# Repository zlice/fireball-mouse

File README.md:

# Fireball mouse

Small PMW3360 fingertip mouse with a magnetic hall sensor joystick for scrolling and single 'fire' button for enter.

Designed for Kailh Mute silent switches (the small 6-7mm box ones) and regular sized mouse switches for left/right click (12-13mm x 5-6mm). Bottom is designed for 4 feet with mounting screws near the back middle for the top shell. The top shell is open for minimal hand contact and weight reduction with no 'middleman' shell.

# Building / Parts

### Part List

 - PWM3360 (desolder from donor or grab some off aliexpress)
 - Kailh Quiet Mute Micro Switches (https://www.kailhswitch.com/micro-switches/mouse-micro-switches/quiet-mute-micro-switches.html - aliexpress or elsewhere)
 - USB4085-GF-A (digikey or newark if out of stock on jlcpcb)
 - M3 0.5x4mm screws (PCB and shell mounting - https://www.amazon.com/gp/product/B0C1SGKGWZ)
 - M3 16mm socket screws (for joystick mount - https://www.amazon.com/gp/product/B07PZ3XXPF)
 - N50 magnets 4x1mm cylinder (aliexpress, alibaba, kj magnets)
 - ABS or PC+PBT 3D printing filament (PushPlastic PBT is what I used for my final version. Spool is not compatible with Bambu AMS btw :])
 - Huano Yellow Dot switches (aliexpress, almost linear if not directly 90 degrees of force - optional)
 - TS02-66-50-BK-160-SCR-D (digikey or newark, small 6mm switch for reset/boot - optional)

### Building

May need tweaking for every printer and filament combo. The bambu project in the [stl](./stl) directory should give the orientations and settings that I used to print.

**general print guide**

 - 0.16mm layer height
 - print bottom separate
 - print top separate
 - print small pieces and side clicks together
 - print left/right clicks together
 - 33mm/s outer shell and overhangs
 - support on the the right finger grip
 - support on the thumb, USB and bottom+top screw mounts (auto worked for these)
 - 6 bottom layers for the bottom
 - rotations for the fire/flip, joystick and clicks are important! (joystick will likely break from screw force if in wrong orientation)

**cleanup**

 - bottom screw mount supports can be punctured and twisted out
 - bottom left thumb overhang needs sanding after support is removed
 - left/right click contacts can be sanded, washed, and electrical taped. But click contact can be very finicky (especially with 'huano yellow dot' switches, I eventually gave up and opted to use the raw plastic). This was the hardest part of 'feel' to get right. Contacts may need moved left/right if you use a 12mm omron style switch vs a kailh square switch.
 - side (forward/backward) clicks support can be a bit messy if you wait for it to cool. Removing supports while warm was easier for me in general but should be done here since the part is small and is less likely to warp or deform while still warm.
 - fire button, side clicks and joystick mount are press fit: print smaller test fits before or you'll have to rig some electrical tape for loose fits, or sand (or break) parts on tight fits.
 - magnetic joystick will need tape over the USB connector to make sure it doesn't contact it. The hall sensor routes **under** the joystick faces **away** from the joystick magnets. Technically the wrong direction, but it works great for me. Another sensor can be placed on the side but is best suited in a similar location on the other side of the joystick. See [ideal locations here](./img/halls.png). The code for the joystick/scroll-stick has been updated to read 10 times and use a +- margin to auto-adjust values for scroll up+down. Logic or values may need changed if the magnets are in different polarity or the sensors are positioned differently (reading different ranges).
 - magnets may need test fits depending on print tolerances. Mine were snug and required no glue to stay in place which is perfect. Make sure they are centered and in the right positions (north/south).
 - if your joystick is squeaky or doesn't move smoothly, sanding the inside with the screw's threads may help. Sanding the edges of the bottom or where parts may rub can help also.
 - tightening PCB mounts should be done evenly and just enough to work with everything else
 - tightening top mounts should be done evenly and just enough to work with clicks, every mm counts for feel here

The PCB will likely not line up 100% !!! Tolerances can vary and you are not always going to get the exact same thing if you don't pay for high tolerances.

Be sure to test fit anyway because anything may be off slightly and it could matter!

# QMK

### Setup

Copy **this** project's qmk `fireball` directory to **qmk_firmware**'s `ploopy` directory.

```sh
git clone https://github.com/qmk/qmk_firmware.git

cp -r qmk/keyboards/ploopyco/fireball qmk_firmware/keyboards/ploopyco/
```

### Compile

In `qmk_firmware`

```sh
qmk compile -kb ploopyco/fireball -km default
```

### Flash

The first time you connect the RP2040 it should be empty and go into boot mode. Once flashed, pressing 'forward' while connecting to USB will enter boot mode, reset/boot buttons may help with a reconnect and boot if needed.

Mount the RP2040 and copy `qmk_firmware/.build/ploopyco_fireball_default.uf2` to the RP2040.

```sh
sudo mount /dev/sda1 /mnt/usb && sudo cp .build/ploopyco_fireball_default.uf2 && sudo umount /mnt/usb
```

# FreeCAD

The finished parts are meshed and provided in the [stl](./stl) directory.

Most of this was copied from my original version. The left and right finger grips were slightly modified but I didn't bother reinventing them because they worked for years great. A lot of confusing FreeCAD methods that you can do one way but not another were used to get make parts. The 'misc' group are left over parts that may break the child parts, test fittings and wires used to sweep/loft/extrude and create cuts and parts.

# KiCAD / jlcpcb

Exporting gerbers/drills is the same as every project I've seen, however for jlcpcb I found multiple tutorials and they all seemed out of date. I used [wokwi's jlcpcb script](https://github.com/wokwi/kicad-jlcpcb-bom-plugin) to make placement files, but still needed to rotate them when setting the PCB assembly up.

- File > Fabcrication outputs > component placement (to /tmp/fireball-components)
- `./kicad_pos_to_cpl.py /tmp/fireball-components/Fireball-top-pos.csv /tmp/fireball-jlcpcb-placement-pos.cmp.csv`

The [jlcpcb](./jlcpcb) directory should be a good start to upload for boards.

You may need to replace some parts if they are out of stock. I think I had to use a TexasInstrument converter instead of one in the BOM.

You will have to trim the 4-pin USB header or desolder for it to fit properly in the shell. This is more for a backup or if you do not want to use a USB-C connector and want a straight wire from mouse to the PC USB. If you do not want a raw cable connection, I would remove it from BOM or PCB before exporting.

# Improvements

- PMW3360 bottom mount is slightly off for me and could be moved/centered better.
- The extra PMW3360 mount square groove in the middle is probably useless and could be removed.
- Thumb groove could be extended up a bit at a 45 degree angle. Your thumb can touch the 'back' button since you are not always flat. I don't accidentally press it and it is not that noticeable or bothersome, but it could be something to look at.
- Hall sensor placement could be better. If the PCB is redone, it may be better to put 2 sensors on the side or directly in front+behind the joystick if possible.
- Fire/flip/enter and joystick may feel better if a bit taller. Left/Right clicks ended up being higher than expected.
- Left/Right click feel is more precise to adjust than I expected. Part of this is due to the light weight top and back mounting. The double prong mounts that commercial mice use help prevent rocking side-to-side which created a very uneven, unpredictable and bad click feel. If I try again it may be ideal to mount clicks directly under where they connect somehow, or at least separately.
- Add capacitors to hall sensor outputs to smooth out noise

# Shoutouts

- Jfedor for the PCB - https://github.com/jfedor2/rp2040-pmw3360
- QMK for the software/firmware and helpful community
- wokwi for the placement script - https://github.com/wokwi/kicad-jlcpcb-bom-plugin

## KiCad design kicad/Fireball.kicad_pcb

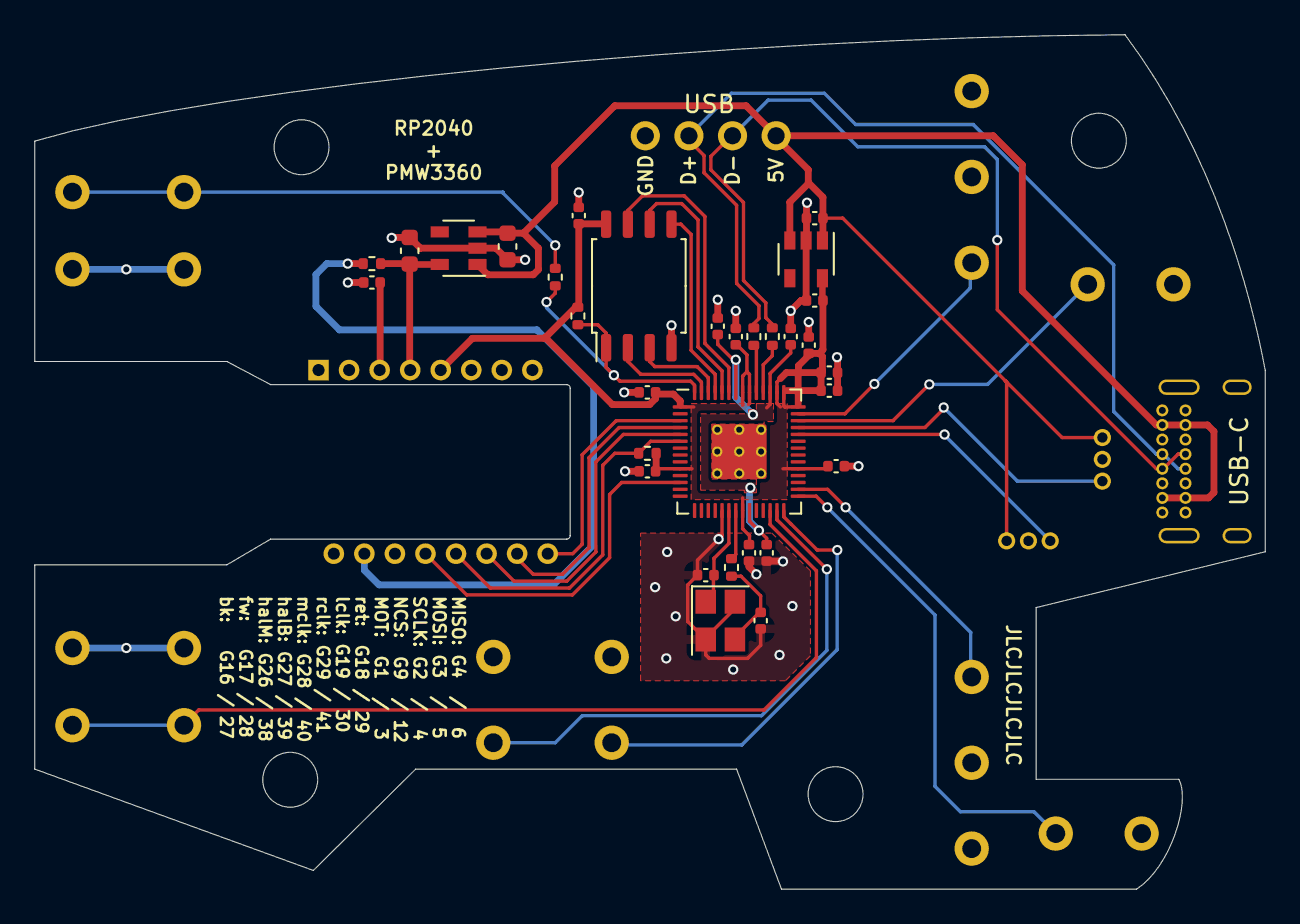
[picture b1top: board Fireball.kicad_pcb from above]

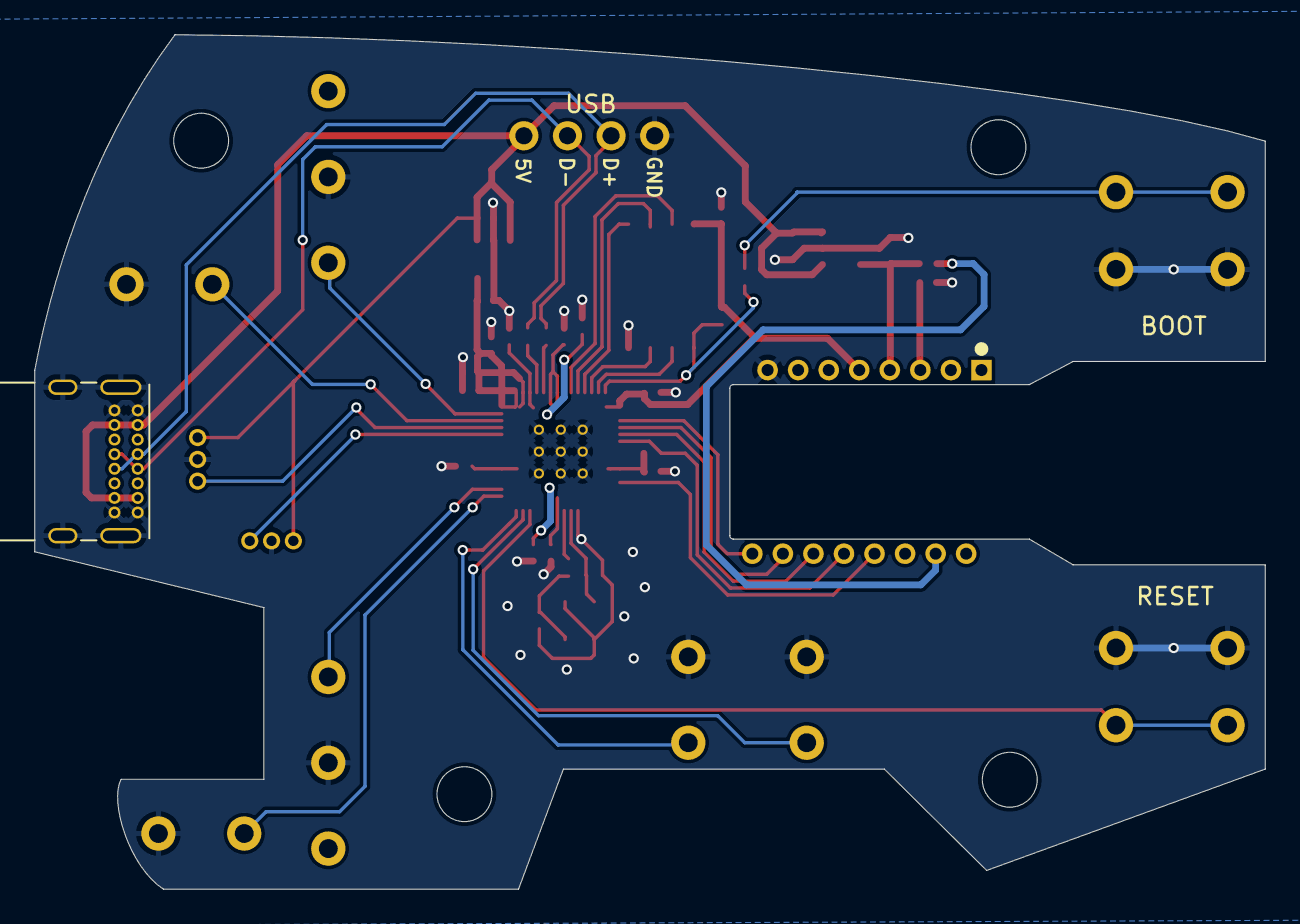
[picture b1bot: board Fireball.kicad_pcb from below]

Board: 2 copper layers, 71.7 x 49.8 mm, 38 parts (2 on the bottom side), 25 nets.

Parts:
C1, C2, C3, C4, C5, C6, C7, C8, C9, C17: 100n; C_0402_1005Metric
C10, C13, C15, C16: 1u; C_0402_1005Metric
C11: 0.1u; C_0603_1608Metric
C12: 1u; C_0603_1608Metric
C14: 4.7u; C_0402_1005Metric
C18, C19: 30p; C_0402_1005Metric
H1, H2, H3, H4: MountingHole; MountingHole_3.2mm_M3
J1: Conn_01x04; PinHeader_1x04_P2.54mm_Vertical
R1: 39; R_0402_1005Metric
R2, R5: 10k; R_0402_1005Metric
R3, R4: 27; R_0402_1005Metric
R6, R7: 1k; R_0402_1005Metric
U1: TCR2EF19; SOT-23-5
U2: PMW3360
U3: RP2040; RP2040-QFN-56
U4: TLV73333PDBV; SOT-23-5
U5: W25Q128JVS; SOIC-8_5.23x5.23mm_P1.27mm
USB-C: USB_C_Receptacle_GCT_USB4085
Y1: Crystal_GND24; Crystal_SMD_3225-4Pin_3.2x2.5mm

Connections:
+1V1: C1.1, C2.1, C13.1, U3.23, U3.45, U3.50
+1V8: C12.1, R1.1, U1.5, U2.4
+3V3: C3.1, C4.1, C5.1, C6.1, C7.1, C8.1, C9.1, C10.1, C16.1, C17.1, R2.1, R5.1, U2.5, U3.1, U3.10, U3.22, U3.33, U3.42, U3.43, U3.44, U3.48, U3.49, U4.5, U5.8
+5V: C11.2, C15.1, J1.1, U1.1, U1.3, U4.1, U4.3, USB-C.A4, USB-C.A9, USB-C.B4, USB-C.B9
D+: J1.3, R3.1, USB-C.A6, USB-C.B6
D-: J1.2, R4.1, USB-C.A7, USB-C.B7
GND: C1.2, C2.2, C3.2, C4.2, C5.2, C6.2, C7.2, C8.2, C9.2, C10.2, C11.1, C12.2, C13.2, C14.2, C15.2, C16.2, C17.2, C18.1, C19.2, J1.4, U1.2, U2.8, U3.19, U3.57, U4.2, U5.4, USB-C.A1, USB-C.A12, USB-C.B1, USB-C.B12, USB-C.S1, Y1.2, Y1.4
MISO: R2.2, U2.12, U3.6
MOSI: U2.11, U3.5
MOTION: U2.9, U3.3
NCS: U2.13, U3.12
unnamed: C14.1, U2.3
unnamed: C19.1, R7.1, Y1.3
unnamed: R1.2, U2.15
unnamed: R3.2, U3.47
unnamed: R4.2, U3.46
QSPI_SCLK: U3.52, U5.6
QSPI_SD0: U3.53, U5.5
QSPI_SD1: U3.55, U5.2
QSPI_SD2: U3.54, U5.3
QSPI_SD3: U3.51, U5.7
QSPI_SS: R5.2, R6.1, U3.56, U5.1
SCLK: U2.10, U3.4
XIN: C18.2, U3.20, Y1.1
XOUT: R7.2, U3.21

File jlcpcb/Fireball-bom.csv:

Id,Designator,Footprint,Quantity,Designation,Supplier and ref
1,"C18,C19",C_0402_1005Metric,2,30p,C1570
2,"C17,C2,C8,C6,C5,C7,C4,C1,C3,C9",C_0402_1005Metric,10,100n,C1525
3,"R6,R7",R_0402_1005Metric,2,1k,C11702
4,"R5,R2",R_0402_1005Metric,2,10k,C25744
5,U3,RP2040-QFN-56,1,RP2040,C2040
6,Y1,Crystal_SMD_3225-4Pin_3.2x2.5mm,1,Crystal_GND24,C9002
7,J1,PinHeader_1x04_P2.54mm_Vertical,1,Conn_01x04,
8,C14,C_0402_1005Metric,1,4.7u,C23733
9,"C10,C16,C15,C13",C_0402_1005Metric,4,1u,C52923
10,"R4,R3",R_0402_1005Metric,2,27,
11,U4,SOT-23-5,1,TLV73333PDBV,C134139
12,R1,R_0402_1005Metric,1,39,C25110
13,U5,SOIC-8_5.23x5.23mm_P1.27mm,1,W25Q128JVS,C97521
14,C12,C_0603_1608Metric,1,1u,C15849
15,C11,C_0603_1608Metric,1,0.1u,C14663
16,U1,SOT-23-5,1,TCR2EF19,

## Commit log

2024-01-07 init
2024-01-07 remove backup freecad
2024-01-11 update hall sensors
2024-01-11 reverse primary hall sensor and update code for auto-value on startup
2024-01-24 todo: capacitors for hall sensor noise
